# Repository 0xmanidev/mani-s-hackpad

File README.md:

# DaVinci Resolve Macropad
this is a project that is developed for me to increase my efficency in video editing apps 

.png)

this macropad provides control through 4 switches and an encoder with switch gives feedback through the led and display and uses xiao Rp2040 as an MCU and it is a2x3 matrix of switches and this is a multi layered setup that switches modes based on encoder switch state 

I used kicad for schematics and pcb design and fusion and thinker cad for case design and hack club community helped a lot in this process 

This uses circuit python and kmk for firmware of the macropad 
I used pyhton to develop the firmware and kmk is a derivative of qmk that is easy to use

made with ❤️ for hack club

**Built by Mani Dev** • MIT License • Made for Hack Club  
[@0xmanidev](https://github.com/0xmanidev) • manikanta.vasamsetti.dev@gmail.com

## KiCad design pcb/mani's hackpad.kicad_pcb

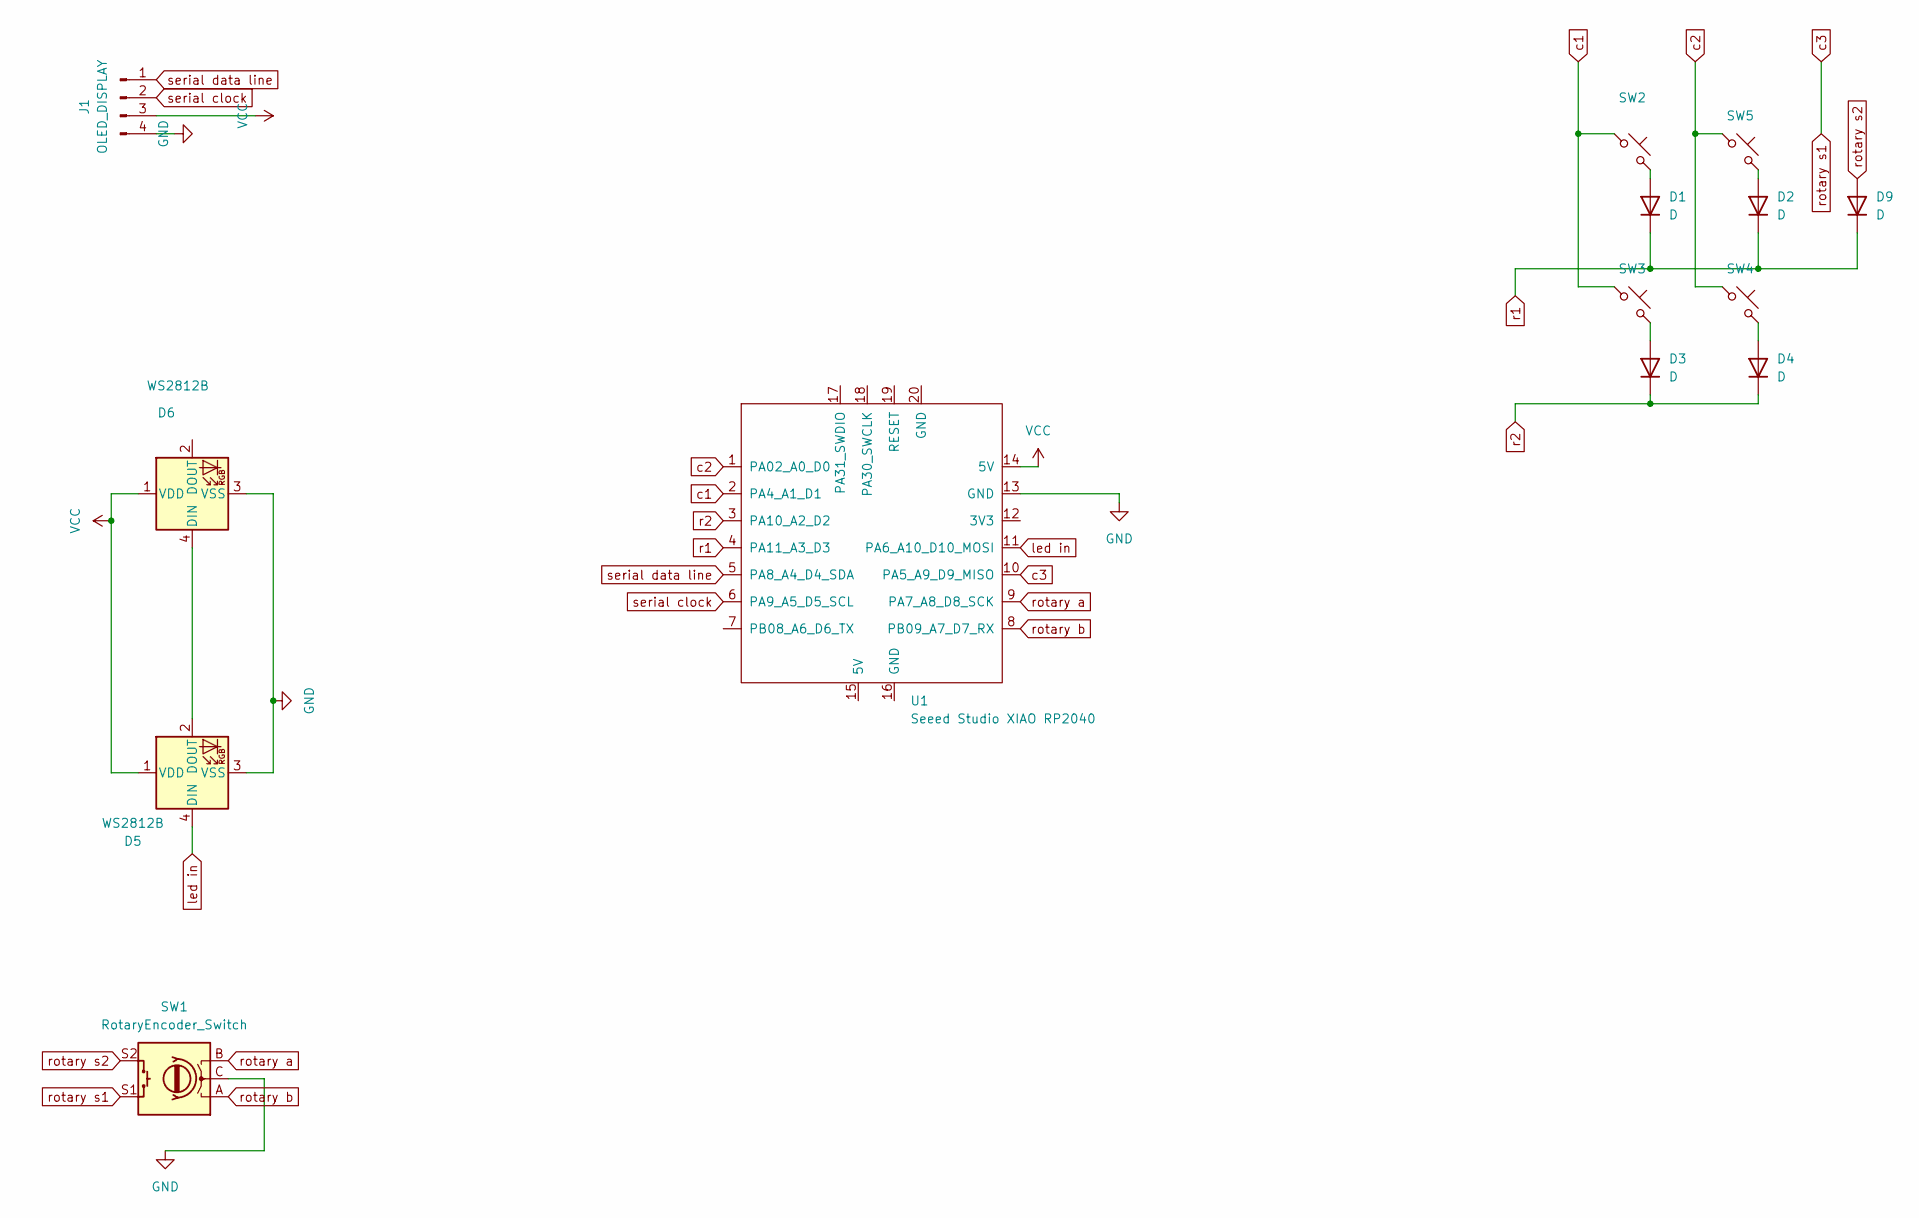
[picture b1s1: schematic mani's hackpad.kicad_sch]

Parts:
D1, D2, D3, D4, D9: D; D_DO-35_SOD27_P7.62mm_Horizontal
D5, D6: WS2812B; LED_WS2812B_PLCC4_5.0x5.0mm_P3.2mm
J1: OLED_DISPLAY; PinHeader_1x04_P2.54mm_Vertical
SW1: RotaryEncoder_Switch; RotaryEncoder_Alps_EC11E-Switch_Vertical_H20mm
SW2, SW3, SW4, SW5: SW_Push_45deg; MX_PCB_1.00u
U1: Seeed Studio XIAO RP2040; XIAO-RP2040-SMD

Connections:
GND: D5.3 (VSS), D6.3 (VSS), J1.4, SW1.C, U1.13 (GND)
unnamed: D1.2 (A), SW2.2
unnamed: D2.2 (A), SW5.2
unnamed: D3.2 (A), SW3.2
unnamed: D4.2 (A), SW4.2
unnamed: D5.2 (DOUT), D6.4 (DIN)
VCC: D5.1 (VDD), D6.1 (VDD), J1.3, U1.14 (5V)
c1: SW2.1, SW3.1, U1.2 (PA4_A1_D1)
c2: SW4.1, SW5.1, U1.1 (PA02_A0_D0)
c3: SW1.S1, U1.10 (PA5_A9_D9_MISO)
led in: D5.4 (DIN), U1.11 (PA6_A10_D10_MOSI)
r1: D1.1 (K), D2.1 (K), D9.1 (K), U1.4 (PA11_A3_D3)
r2: D3.1 (K), D4.1 (K), U1.3 (PA10_A2_D2)
rotary a: SW1.B, U1.9 (PA7_A8_D8_SCK)
rotary b: SW1.A, U1.8 (PB09_A7_D7_RX)
rotary s2: D9.2 (A), SW1.S2
serial clock: J1.2, U1.6 (PA9_A5_D5_SCL)
serial data line: J1.1, U1.5 (PA8_A4_D4_SDA)

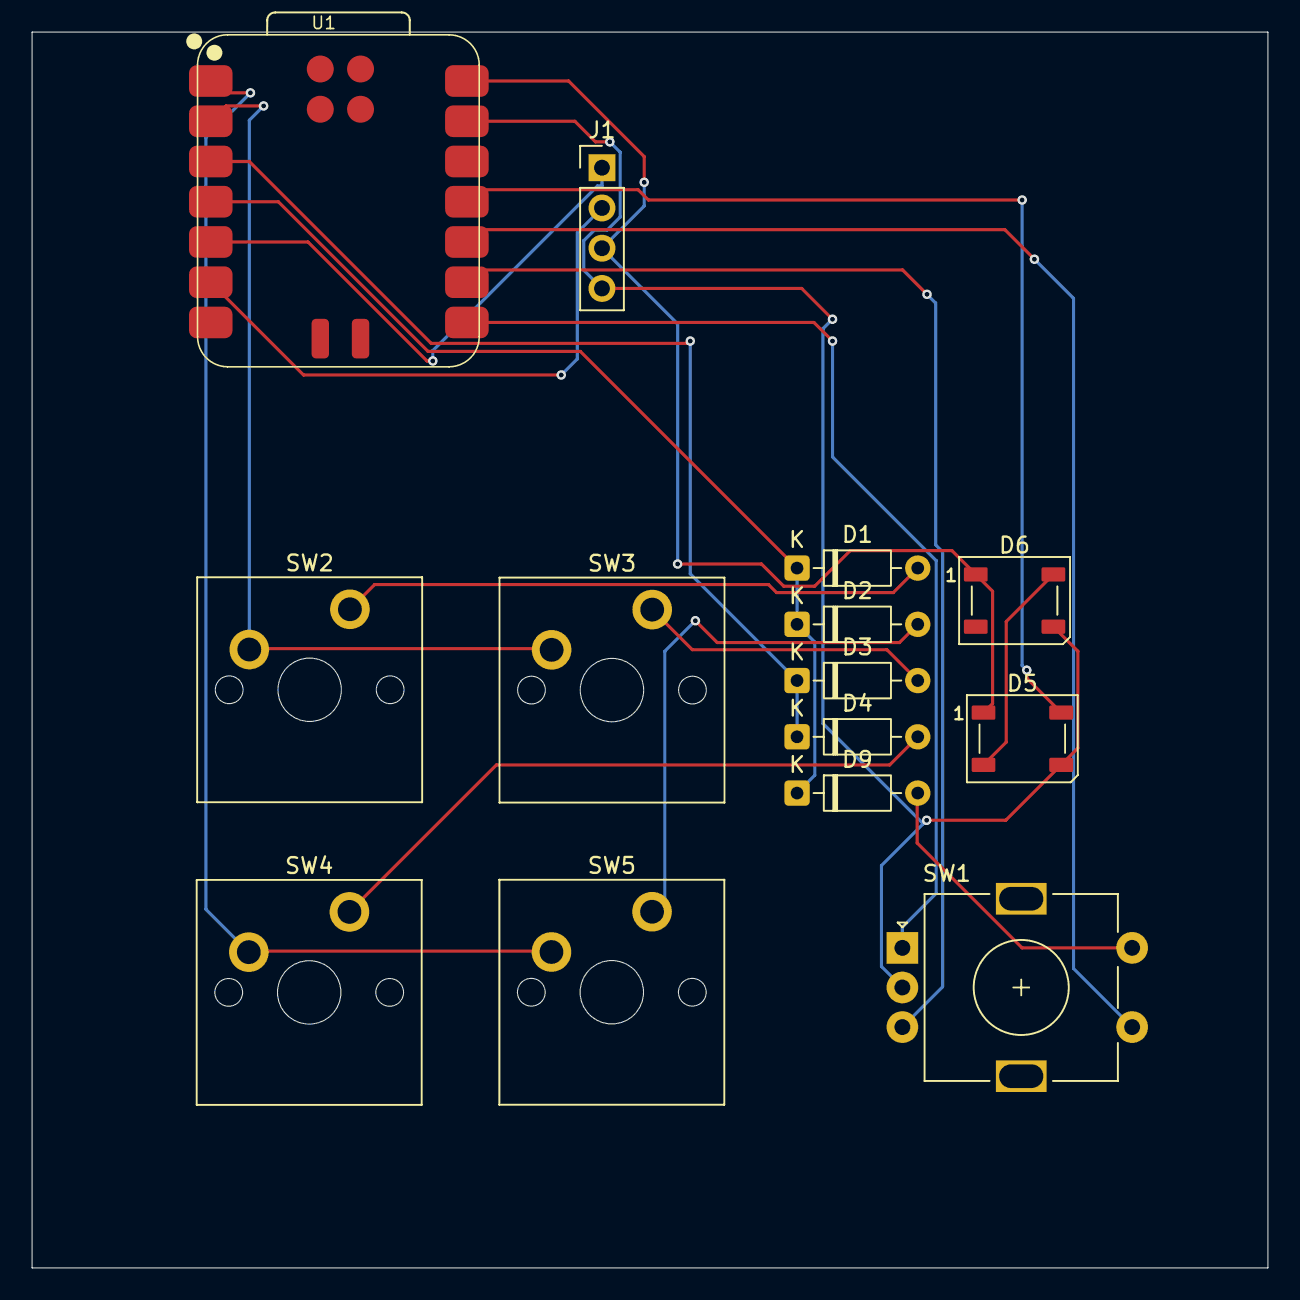
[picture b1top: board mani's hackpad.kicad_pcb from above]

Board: 2 copper layers, 78.0 x 78.0 mm, 14 parts (0 on the bottom side), 18 nets.

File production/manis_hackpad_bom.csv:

Designator,Footprint,Quantity,Value,LCSC Part #
"D1, D2, D3, D4, D9",D_DO-35_SOD27_P7.62mm_Horizontal,5,D,
"D5, D6",LED_WS2812B_PLCC4_5.0x5.0mm_P3.2mm,2,WS2812B,
J1,PinHeader_1x04_P2.54mm_Vertical,1,OLED_DISPLAY,
SW1,RotaryEncoder_Alps_EC11E-Switch_Vertical_H20mm,1,RotaryEncoder_Switch,
"SW2, SW3, SW4, SW5",MX_PCB_1.00u,4,SW_Push_45deg,
U1,XIAO-RP2040-SMD,1,Seeed Studio XIAO RP2040,

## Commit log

2026-03-16 Create JOURNAL.md with macropad project details
    Added a journal entry detailing the macropad design for video editing.
2026-03-20 cad files
2026-03-20 readme
2026-03-20 small change
2026-03-20 changes in readme
2026-03-20 formatting readme
2026-03-20 sry my profile link isn't working
2026-03-21 reformatting readme
2026-03-21 heading
2026-03-21 f3d files added
2026-03-21 photo
2026-03-21 photo retry
2026-03-21 photo retry 2
2026-03-22 readme update
2026-03-22 assembly
2026-03-23 Revise README with project details and setup instructions
    Updated project description and details about the macropad's functionality, setup, and controls. Added information about tools used in the design process and firmware development.
2026-03-23 upload files
2026-03-23 upload
